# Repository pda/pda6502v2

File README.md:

pda6502v2
=========

pda6502v2 is a single-board homebrew computer built around the 8-bit
[6502][6502] CPU, varitions of which powered the venerable [Commodore 64][c64],
[Apple II][appleii], [Nintendo Entertainment System][nes] and lots more.

This repository contains all aspects of its development:

| Directory             | Description                      | Language / Tool |
| --------------------- | -------------------------------- | --------------- |
| [`kicad/`](kicad)     | hardware schematic / PCB design  | KiCad           |
| [`bifröst/`](bifröst) | BIFRÖST FPGA system controller   | Verilog         |
| [`os/`](os)           | pda6502v2 firmware/OS/software   | 6502 assembly   |
| [`emu/`](emu)         | pda6502v2 emulator               | Rust            |
| [`eeprog/`](eeprog)   | SPI EEPROM in-circuit programmer | C, Arduino C++  |

Hardware specifications
-----------------------

- 6502 CPU ([WDC 65C02][W65C02])
- “BIFRÖST” FPGA system controller ([Lattice ICE40HX4K][ice40])
- 512 KiB static RAM
- 2 x [6522 VIA][W65C22]; 4 x 8-bit ports; 32 GPIO pins
- [SID][sid] sound generator ([ARMSID][armsid])
- SPI controller (BIFRÖST FPGA)
- UART ([NXP SC28L92 dual UART][nxpuart])

Compared to original pda6502
----------------------------

pda6502v2 is redesigned from scratch to address the pain points encountered
creating and programming the original [pda6502][pda6502]
several years earlier:

* Tedious software/bootloader development cycle, physically removing and slowly
  reprogramming an EEPROM on every software iteration.
* Limited, very slow SPI communications (bit-banged via 6522 GPIO) not viable
  for SPI displays etc.
* No UART for serial console or other communications with modern systems.
* Inflexible address bus mapping with hard-wired logic gates.

These issues and more have been improved:

|                       | pda6502             | pda6502v2                             |
| --------------------- | ------------------- | ------------------------------------- |
| Bootloader / firmware | EEPROM              | In-circuit programmable Flash EEPROM  |
| SPI                   | 6522 bit-bang       | FPGA hardware accelerated             |
| UART                  | *none*              | Dual UART (SC28L92)                   |
| GPIO                  | 6522 VIA            | Dual 6522 VIA                         |
| Sound                 | *none*              | ARMSID (SID emulation)                |
| RAM                   | 32 KiB              | 512 KiB (FPGA can bank-switch)        |
| Clock                 | 1 MHz oscillator    | FPGA generated; variable              |
| Address decode logic  | 7400-series chips   | FPGA programmable                     |
| Voltage               | 5.0V                | 3.3V                                  |
| Schematic/layout tool | EAGLE               | KiCad                                 |

FPGA system controller: BIFRÖST
-------------------------------

An FPGA (Lattice ICE40HX4K-TQ144) acts as a system controller (dubbed BIFRÖST)
with three primary functions;

### System startup

Startup code is stored in an on-board SPI serial EEPROM (Microchip AT25M01)
which can be written from an external computer via SPI ICSP header.

(Microchip AT25M01 replaced by ON Semiconductor CAT25M01 due to availability).

BIFRÖST bootstraps the system by copying a fixed size/location bootloader from
serial EEPROM into main RAM before starting CPU.  The bootloader may load
further code/data from the serial EEPROM.

This solves the main pain point of version one, in which program/bootloader
development involved removing and rewriting an EEPROM on every development
iteration.

### Address logic

Mapping of the address space to SRAM and I/O chips is also handled by BIFRÖST.
This provide very low propagation time allowing for fast clock speed, and is
in-circuit programmable for flexible address space / logic design without
hardware changes.

BIFRÖST has the entire address bus, data bus, control signals and clock,
allowing for arbitrary address mapping. For example a control register could be
exposed for state-based mapping, e.g. memory layer switching like the Commodore
64.

### BIFRÖST chip selection / considerations

BIFRÖST is implemented as a Lattice ICE40HX4K-TQ144 FPGA with a Microchip
AT25M01 SPI flash EEPROM for configuration storage. The EEPROM also acts as
the 6502 system ROM, loaded into RAM by BIFRÖST during boot.

Any signal that can be routed through / controlled by BIFRÖST should be, so
that design decisions are pushed from hardware schematic and into FPGA HDL
which can be easily altered after assembly.

BIFRÖST needs the following signals:

| Signals                                                                       | Count   |
| ----------------------------------------------------------------------------- | ------- |
| Bus: `ADDR 0..15` + extended `ADDR 16..18`                                    | **19**  |
| SPI: `MISO`, `MOSI`, `SCLK`, `SS` x 8                                         | **11**  |
| 6502: `CLK` `RWB` `BE` `IRQB` `MLB` `NMIB` `RDY` `SOB` `SYNC` `VPB` `RESB`    | **10**  |
| UART: `CS`, `IM`, `IRQ`, `RDN`, `RXAIRQ`, `RXBIRQ`, `TXAIRQ`, `TXBIRQ`, `WRN` | **9**   |
| Bus: `DATA 0..7`                                                              | **8**   |
| VIA1 & VIA2: `CS`, `IRQ`                                                      | **4**   |
| SRAM `CS`                                                                     | **1**   |
| `CLOCKSRC` (in from oscillator)                                               | **1**   |
| `~RESET`                                                                      | **1**   |

This brings the total I/O pin requirement to at least 64.

The ICE40HX1K-VQ100 FPGA lacks PLL; PLL could be useful?

The TQ144 package includes PLL and has the same 0.5 mm pitch, so shouldn't be
materially harder to hand-solder.

The ICE40HX**4**K is bigger/better, with immaterial cost difference at this
volume.

RAM
---

Alliance Memory AS6C4008-55PCN 512K x 8 SRAM with 55ns access time at 2.7~5.5V
in a PDIP-32 package provides 512 KiB RAM.

This is 8 times larger than the 6502's 16-bit address space; access to RAM
beyond the first 64 KiB is managed by BIFRÖST.

(Earlier during system design, a pair of AS6C62256 32K x 8 PDIP-28 was chosen
to provide a less overkill and more era-appropriate 64 KiB of RAM, then lure of
1 MiB RAM made that 2 x 512 KiB, then the second 512 KiB was removed to make
PCB space for SID.

I/O
---

- SPI: 8 devices
- GPIO: 2 x 6522 VIA providing total of 4 x 8-bit ports
- Dual UART
- SID (ARMSID) sound

### SPI

BIFRÖST maps registers into the 6502 address space, implementing SPI master
similar to http://6502.org/users/andre/spi65b/index.html

This hardware SPI communication is orders of magnitude faster than 6522
bit-banging, making SPI display output more viable.

### GPIO

A pair of WDC W65C22S (6522) VIA provide two 8-bit GPIO ports each, as well as timers etc.

### UART

NXP SC28L92 3.3V dual UART (SC28L92A1A: PLC44-44 package)

Useful information on [UARTs: REPLACING THE 65C51 on 6502.org forums](http://forum.6502.org/viewtopic.php?f=4&t=4587).

### SID Sound

[ARMSID][armsid] emulates MOS6581 or MOS8580 SID.

I believe this will only function correctly when running at ~1 MHz.

An email reply from the creator re. voltage and clock:

> The ARMSID has its own LDO regulator, so it needs at least 3.45 V (max. 5.5 V) on pin 24 for proper operation.
> The value of the output signals is logic 3.3 V, the inputs are tolerant to 5 V. Therefore, it is not a problem to connect it to a 3.3 V system.
> The clock signal is designed for use in the C64, so it is guaranteed in the range of 0.985 to 1.023 MHz and directly controls the emulation rate (just like the original SID).
> Lower frequencies are not a problem, higher frequencies can disable emulation. All write and read operations should take at least 350ns for proper operation.

Power supply & reset
--------------------

TLV1117-33 LDO linear regulator brings 4.75V–15V down to the main 3.3V / 800mA
supply, used for all internal/external I/O.

LT3030 dual LDO linear regulator brings the 3.3V supply down to 2.5V / 750mA
and 1.2V / 250mA for the additional FPGA voltage requirements.

The In-Circuit System Programming (ICSP) header can power the AT25M01 SPI flash
EEPROM (1.7–5.5V) only, isolated from the rest of the system via 1N4148 Diode.

Maxim DS1818-5 “3.3V EconoReset with Pushbutton” handles holding RESET
active-low during power-on, brown-out, and when a RESET button is pressed.

Memory map
----------

Memory mapping is controlled by BIFRÖST, so it may be reconfigured.
Currently, everything is RAM except 0xD000–DFFF.

- `0xD400` SID (nobomi ARMSID)
- `0xDC00` VIA1 (WDC 65C22)
- `0xDC10` VIA2 (WDC 65C22)
- `0xDC20` UART (NXP SC28L92)

This roughly matches Commodore 64's I/O space.

Errata
------

R26 (0 ohm) and R27 (open) labels are swapped.
The one closer to LT3030 vreg is R26 and should be 0 ohm (jumper/shorted).
The one further from the LT3030 vreg is R27 and should be open (not connected).

EEPROM triple drama:
- 128 KiB isn't nearly enough; iCEstick has 4 MiB.
- missing pull-up on SPI CS to put FPGA into SPI master mode.
- MISO/MOSI lines from FPGA to EEPROM are swapped :(
The best solution to this mess is to leave the EEPROM footprint unpopulated,
and attach a small board to ICSP header with:
- a larger EEPROM,
- a 10K pull-up resistor on CS,
- a MISO/MOSI-correct ICSP header.
A prototype of this works using a Winbond W25Q80BVAIG 8Mbit SPI EEPROM.
(Silver lining: attempts to program the EEPROM while it's connected to the FPGA
have failed, despite efforts to make the FPGA tristate those SPI lines when not
in use. Being able to disconnect the EEPROM from the FPGA is useful. However
one of the pda6502v2 goals was uploading new 6502 code without touching the
board. Hopefully this can be fixed in Verilog.

RESET lines for BIFRÖST FPGA and the 6502 system are coupled.  This is a
terrible idea; BIFRÖST needs to reset the CPU without resetting itself.
Workaround: use a knife to physically cut the RESET trace coming from top-right
pin of RESET switch, next to pin 1 of ARMSID, and then airwire from EXT[0] to
6502 RESET.

[6502]: http://en.wikipedia.org/wiki/MOS_Technology_6502
[W65C02]: http://en.wikipedia.org/wiki/WDC_65C02
[W65C22]: http://en.wikipedia.org/wiki/WDC_65C22
[appleii]: https://en.wikipedia.org/wiki/Apple_II
[armsid]: https://www.nobomi.cz/8bit/armsid/index_en.php
[c64]: https://en.wikipedia.org/wiki/Commodore_64
[ice40]: https://www.latticesemi.com/iCE40
[nes]: https://en.wikipedia.org/wiki/Nintendo_Entertainment_System
[nxpuart]: https://www.nxp.com/products/interfaces/uarts/3-3-v-5-0-v-dual-universal-asynchronous-receiver-transmitter-duart:SC28L92
[sid]: https://en.wikipedia.org/wiki/MOS_Technology_6581
[pda6502]: https://github.com/pda/pda6502

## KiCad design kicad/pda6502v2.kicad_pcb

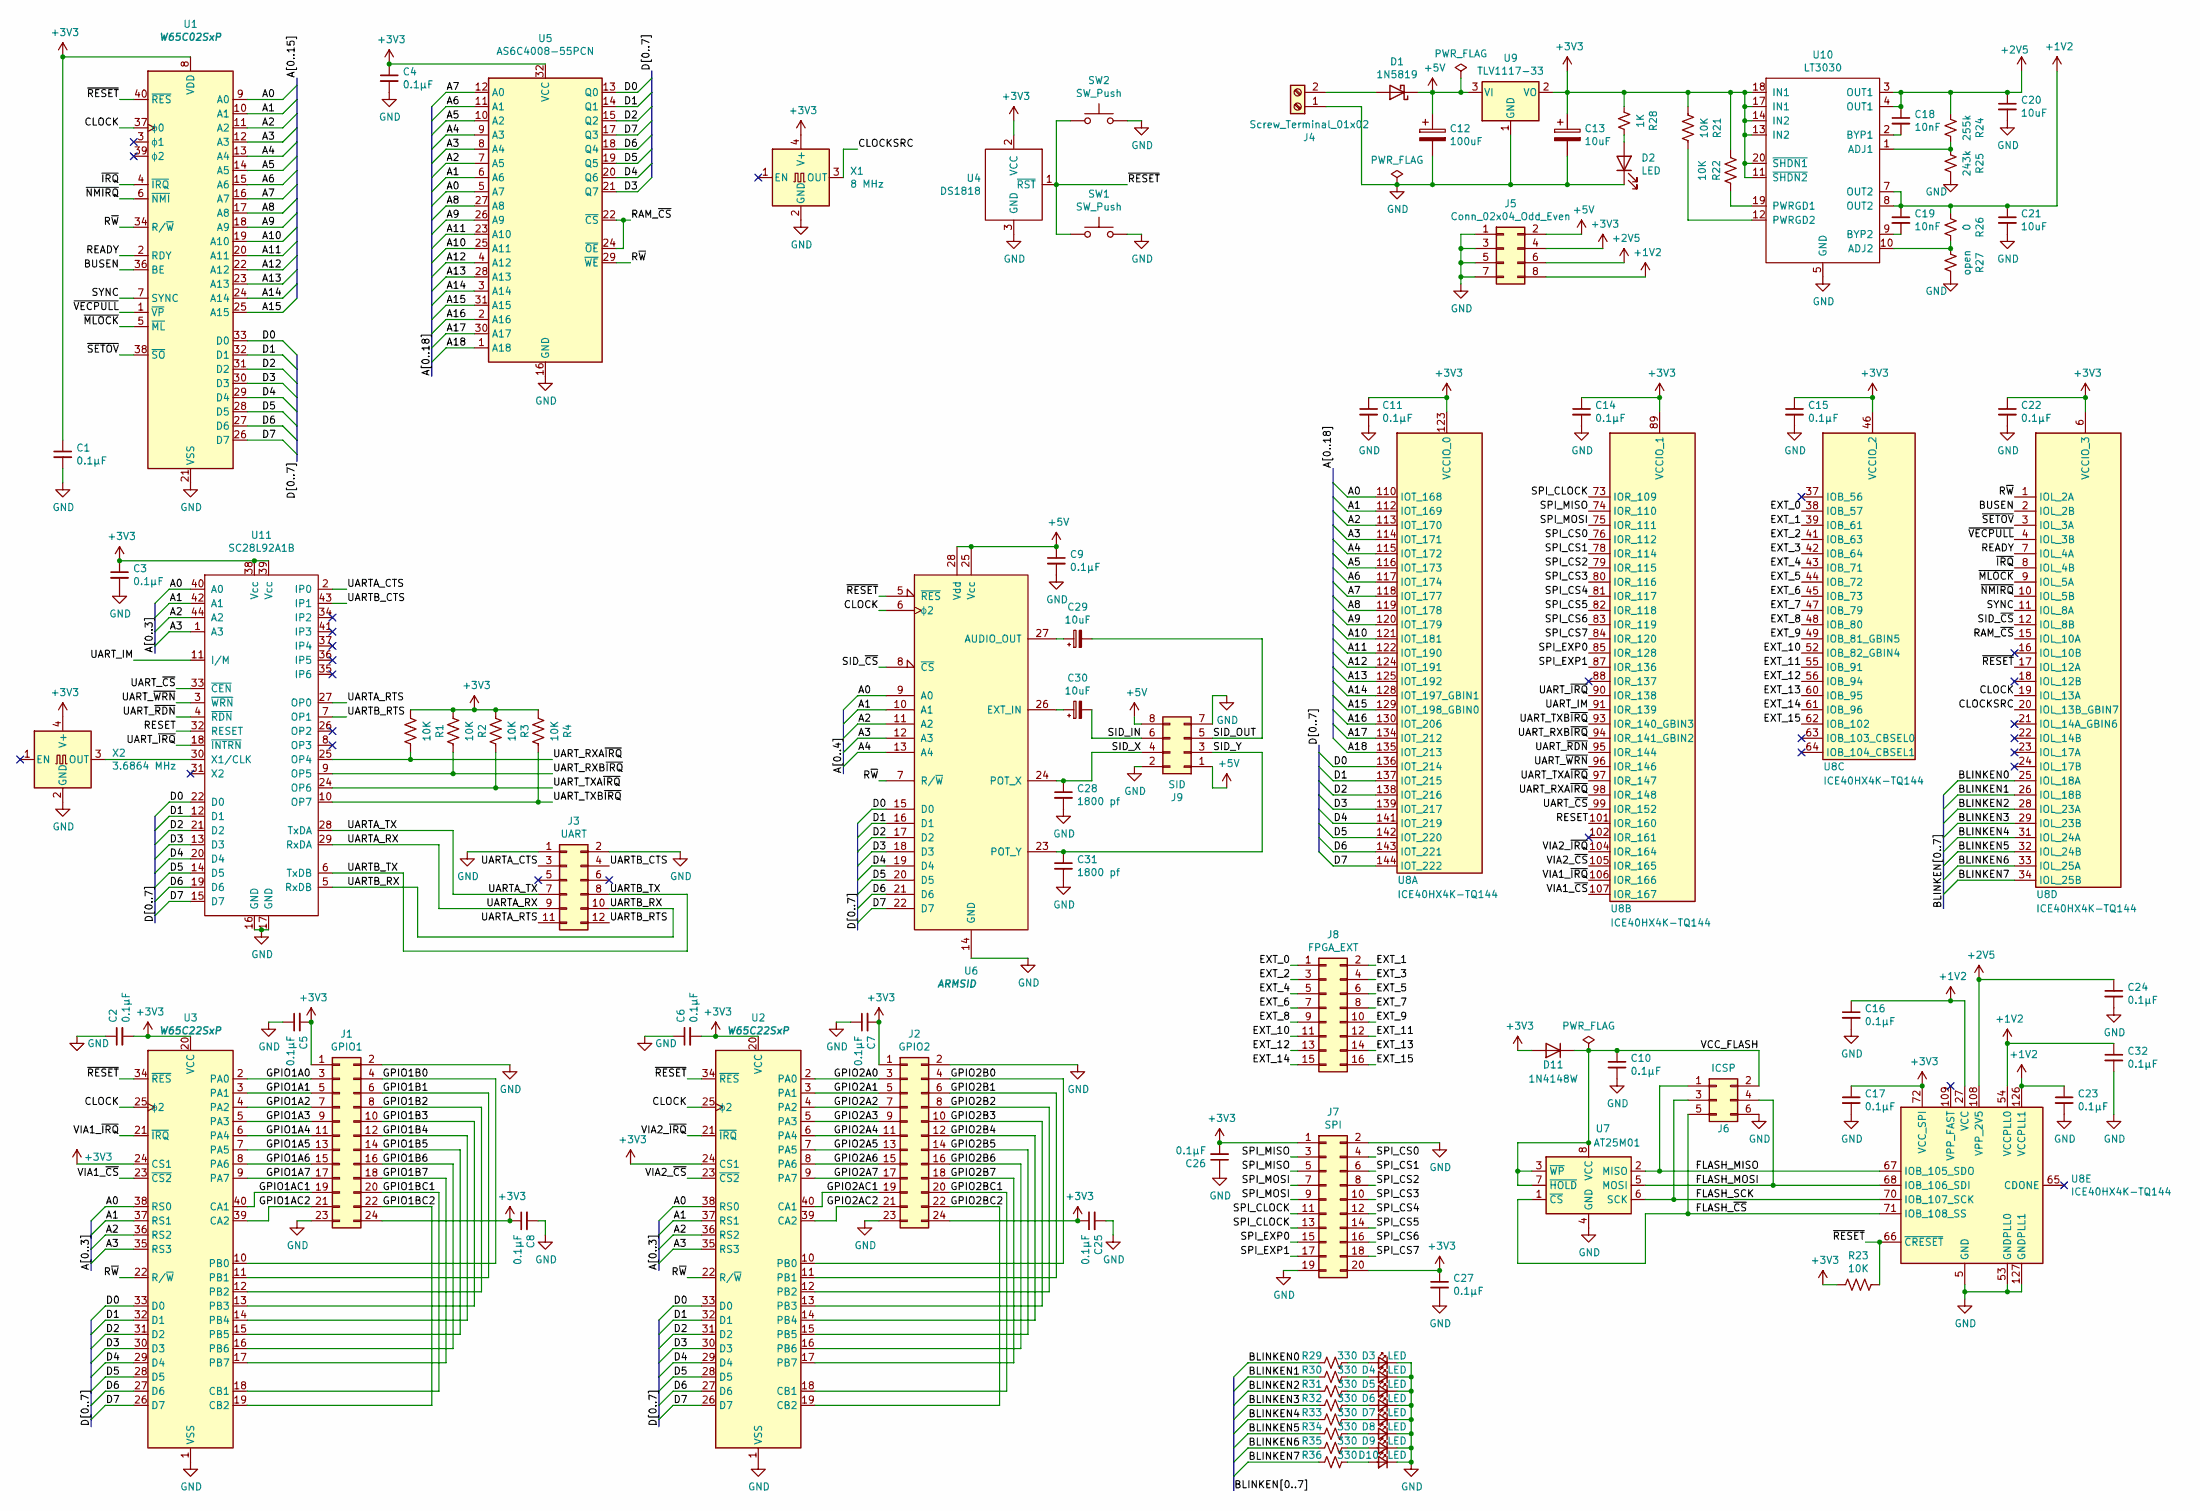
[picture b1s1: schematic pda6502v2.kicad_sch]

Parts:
C1, C2, C3, C4, C5, C6, C7, C8, C9, C10, C11, C14, C15, C16, C17, C22, C23, C24, C25, C26, C27, C32: 0.1μF; C_0805_2012Metric_Pad1.18x1.45mm_HandSolder
C12: 100uF; CP_Radial_D5.0mm_P2.00mm
C13: 10uF; CP_Radial_D5.0mm_P2.00mm
C18, C19: 10nF; C_0805_2012Metric_Pad1.18x1.45mm_HandSolder
C20, C21: 10uF; C_0805_2012Metric_Pad1.18x1.45mm_HandSolder
C28, C31: 1800 pf; C_0805_2012Metric_Pad1.18x1.45mm_HandSolder
C29, C30: 10uF; CP_EIA-3528-15_AVX-H_Pad1.50x2.35mm_HandSolder
D1: 1N5819; D_DO-41_SOD81_P10.16mm_Horizontal
D2: LED; LED_D3.0mm
D3, D4, D5, D6, D7, D8, D9, D10: LED; LED_0805_2012Metric_Pad1.15x1.40mm_HandSolder
D11: 1N4148W; D_SOD-123
J1: GPIO1; PinHeader_2x12_P2.54mm_Vertical
J2: GPIO2; PinHeader_2x12_P2.54mm_Vertical
J3: UART; PinHeader_2x06_P2.54mm_Vertical
J4: Screw_Terminal_01x02; TerminalBlock_Phoenix_MPT-0,5-2-2.54_1x02_P2.54mm_Horizontal
J5: Conn_02x04_Odd_Even; PinHeader_2x04_P2.54mm_Vertical
J6: ICSP; PinHeader_2x03_P2.54mm_Vertical
J7: SPI; PinHeader_2x10_P2.54mm_Vertical
J8: FPGA_EXT; PinHeader_2x08_P2.54mm_Vertical
J9: SID; PinHeader_2x04_P2.54mm_Vertical
R1, R2, R3, R4, R21, R22, R23: 10K; R_0805_2012Metric_Pad1.20x1.40mm_HandSolder
R24: 255k; R_0805_2012Metric_Pad1.20x1.40mm_HandSolder
R25: 243k; R_0805_2012Metric_Pad1.20x1.40mm_HandSolder
R26: 0; R_0805_2012Metric_Pad1.20x1.40mm_HandSolder
R27: open; R_0805_2012Metric_Pad1.20x1.40mm_HandSolder
R28: 1K; R_0805_2012Metric_Pad1.20x1.40mm_HandSolder
R29, R30, R31, R32, R33, R34, R35, R36: 330; R_0805_2012Metric_Pad1.20x1.40mm_HandSolder
SW1: SW_Push; SW_PUSH_6mm_H5mm
SW2: SW_Push; PinHeader_1x02_P2.54mm_Vertical
U1: W65C02SxP; DIP-40_W15.24mm
U2, U3: W65C22SxP; DIP-40_W15.24mm
U4: DS1818; SOT-23_Handsoldering
U5: AS6C4008-55PCN; DIP-32_W15.24mm
U6: ARMSID; DIP-28_W15.24mm_Socket
U7: AT25M01; SOIC-8_3.9x4.9mm_P1.27mm
U8: ICE40HX4K-TQ144; TQFP-144_20x20mm_P0.5mm
U9: TLV1117-33; SOT-223
U10: LT3030; HTSSOP-20-1EP_4.4x6.5mm_P0.65mm_EP2.85x4mm
U11: SC28L92A1B; PQFP-44_10x10mm_P0.8mm
X1: 8 MHz; Oscillator_SMD_EuroQuartz_XO53-4Pin_5.0x3.2mm
X2: 3.6864 MHz; Oscillator_SMD_EuroQuartz_XO53-4Pin_5.0x3.2mm

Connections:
+1V2: C16.1, C19.1, C21.1, C23.1, C32.1, J5.8, R26.2, U8.27 (VCC), U8.40 (VCC), U8.54 (VCCPLL0), U8.92 (VCC), U8.111 (VCC), U8.126 (VCCPLL1), U10.7 (OUT2), U10.8 (OUT2)
+2V5: C18.1, C20.1, C24.1, J5.6, R24.2, U8.108 (VPP_2V5), U10.3 (OUT1), U10.4 (OUT1)
+5V: C9.1, C12.1, D1.1 (K), J5.2, J9.1, J9.8, U6.25 (Vcc), U6.28 (Vdd), U9.3 (VI)
/A0: U1.9 (A0), U2.38 (RS0), U3.38 (RS0), U5.5 (A7), U6.9 (A0), U8.110 (IOT_168), U11.40 (A0)
/A1: U1.10 (A1), U2.37 (RS1), U3.37 (RS1), U5.6 (A6), U6.10 (A1), U8.112 (IOT_169), U11.42 (A1)
/A2: U1.11 (A2), U2.36 (RS2), U3.36 (RS2), U5.7 (A5), U6.11 (A2), U8.113 (IOT_170), U11.44 (A2)
/A3: U1.12 (A3), U2.35 (RS3), U3.35 (RS3), U5.8 (A4), U6.12 (A3), U8.114 (IOT_171), U11.1 (A3)
/A4: U1.13 (A4), U5.9 (A3), U6.13 (A4), U8.115 (IOT_172)
/A5: U1.14 (A5), U5.10 (A2), U8.116 (IOT_173)
/A6: U1.15 (A6), U5.11 (A1), U8.117 (IOT_174)
/A7: U1.16 (A7), U5.12 (A0), U8.118 (IOT_177)
/A8: U1.17 (A8), U5.27 (A8), U8.119 (IOT_178)
/A9: U1.18 (A9), U5.26 (A9), U8.120 (IOT_179)
/A10: U1.19 (A10), U5.25 (A11), U8.121 (IOT_181)
/A11: U1.20 (A11), U5.23 (A10), U8.122 (IOT_190)
/A12: U1.22 (A12), U5.4 (A12), U8.124 (IOT_191)
/A13: U1.23 (A13), U5.28 (A13), U8.125 (IOT_192)
/A14: U1.24 (A14), U5.3 (A14), U8.128 (IOT_197_GBIN1)
/A15: U1.25 (A15), U5.31 (A15), U8.129 (IOT_198_GBIN0)
/A16: U5.2 (A16), U8.130 (IOT_206)
/A17: U5.30 (A17), U8.134 (IOT_212)
/A18: U5.1 (A18), U8.135 (IOT_213)
/BLINKEN0: R29.2, U8.25 (IOL_18A)
/BLINKEN1: R30.2, U8.26 (IOL_18B)
/BLINKEN2: R31.2, U8.28 (IOL_23A)
/BLINKEN3: R32.2, U8.29 (IOL_23B)
/BLINKEN4: R33.2, U8.31 (IOL_24A)
/BLINKEN5: R34.2, U8.32 (IOL_24B)
/BLINKEN6: R35.2, U8.33 (IOL_25A)
/BLINKEN7: R36.2, U8.34 (IOL_25B)
/BUSEN: U1.36 (BE), U8.2 (IOL_2B)
/CLOCK: U1.37 (ϕ0), U2.25 (ϕ2), U3.25 (ϕ2), U6.6 (ϕ2), U8.19 (IOL_13A)
/CLOCKSRC: U8.20 (IOL_13B_GBIN7), X1.3 (OUT)
/D0: U1.33 (D0), U2.33 (D0), U3.33 (D0), U5.13 (Q0), U6.15 (D0), U8.136 (IOT_214), U11.22 (D0)
/D1: U1.32 (D1), U2.32 (D1), U3.32 (D1), U5.14 (Q1), U6.16 (D1), U8.137 (IOT_215), U11.12 (D1)
/D2: U1.31 (D2), U2.31 (D2), U3.31 (D2), U5.15 (Q2), U6.17 (D2), U8.138 (IOT_216), U11.21 (D2)
/D3: U1.30 (D3), U2.30 (D3), U3.30 (D3), U5.21 (Q7), U6.18 (D3), U8.139 (IOT_217), U11.13 (D3)
/D4: U1.29 (D4), U2.29 (D4), U3.29 (D4), U5.20 (Q6), U6.19 (D4), U8.141 (IOT_219), U11.20 (D4)
/D5: U1.28 (D5), U2.28 (D5), U3.28 (D5), U5.19 (Q5), U6.20 (D5), U8.142 (IOT_220), U11.14 (D5)
/D6: U1.27 (D6), U2.27 (D6), U3.27 (D6), U5.18 (Q4), U6.21 (D6), U8.143 (IOT_221), U11.19 (D6)
/D7: U1.26 (D7), U2.26 (D7), U3.26 (D7), U5.17 (Q3), U6.22 (D7), U8.144 (IOT_222), U11.15 (D7)
/EXT_0: J8.1, U8.38 (IOB_57)
/EXT_1: J8.2, U8.39 (IOB_61)
/EXT_2: J8.3, U8.41 (IOB_63)
/EXT_3: J8.4, U8.42 (IOB_64)
/EXT_4: J8.5, U8.43 (IOB_71)
/EXT_5: J8.6, U8.44 (IOB_72)
/EXT_6: J8.7, U8.45 (IOB_73)
/EXT_7: J8.8, U8.47 (IOB_79)
/EXT_8: J8.9, U8.48 (IOB_80)
/EXT_9: J8.10, U8.49 (IOB_81_GBIN5)
/EXT_10: J8.11, U8.52 (IOB_82_GBIN4)
/EXT_11: J8.12, U8.55 (IOB_91)
/EXT_12: J8.13, U8.56 (IOB_94)
/EXT_13: J8.14, U8.60 (IOB_95)
/EXT_14: J8.15, U8.61 (IOB_96)
/EXT_15: J8.16, U8.62 (IOB_102)
/FLASH_MISO: J6.1, U7.2 (MISO), U8.67 (IOB_105_SDO)
/FLASH_MOSI: J6.4, U7.5 (MOSI), U8.68 (IOB_106_SDI)
/FLASH_SCK: J6.3, U7.6 (SCK), U8.70 (IOB_107_SCK)
/FLASH_~CS: J6.5, U7.1 (~CS), U8.71 (IOB_108_SS)
/GPIO1A0: J1.3, U3.2 (PA0)
/GPIO1A1: J1.5, U3.3 (PA1)
/GPIO1A2: J1.7, U3.4 (PA2)
/GPIO1A3: J1.9, U3.5 (PA3)
/GPIO1A4: J1.11, U3.6 (PA4)
/GPIO1A5: J1.13, U3.7 (PA5)
/GPIO1A6: J1.15, U3.8 (PA6)
/GPIO1A7: J1.17, U3.9 (PA7)
/GPIO1AC1: J1.19, U3.40 (CA1)
/GPIO1AC2: J1.21, U3.39 (CA2)
/GPIO1B0: J1.4, U3.10 (PB0)
/GPIO1B1: J1.6, U3.11 (PB1)
/GPIO1B2: J1.8, U3.12 (PB2)
/GPIO1B3: J1.10, U3.13 (PB3)
/GPIO1B4: J1.12, U3.14 (PB4)
/GPIO1B5: J1.14, U3.15 (PB5)
/GPIO1B6: J1.16, U3.16 (PB6)
/GPIO1B7: J1.18, U3.17 (PB7)
/GPIO1BC1: J1.20, U3.18 (CB1)
/GPIO1BC2: J1.22, U3.19 (CB2)
/GPIO2A0: J2.3, U2.2 (PA0)
/GPIO2A1: J2.5, U2.3 (PA1)
/GPIO2A2: J2.7, U2.4 (PA2)
/GPIO2A3: J2.9, U2.5 (PA3)
/GPIO2A4: J2.11, U2.6 (PA4)
/GPIO2A5: J2.13, U2.7 (PA5)
/GPIO2A6: J2.15, U2.8 (PA6)
/GPIO2A7: J2.17, U2.9 (PA7)
/GPIO2AC1: J2.19, U2.40 (CA1)
/GPIO2AC2: J2.21, U2.39 (CA2)
/GPIO2B0: J2.4, U2.10 (PB0)
/GPIO2B1: J2.6, U2.11 (PB1)
/GPIO2B2: J2.8, U2.12 (PB2)
/GPIO2B3: J2.10, U2.13 (PB3)
/GPIO2B4: J2.12, U2.14 (PB4)
/GPIO2B5: J2.14, U2.15 (PB5)
/GPIO2B6: J2.16, U2.16 (PB6)
/GPIO2B7: J2.18, U2.17 (PB7)
/GPIO2BC1: J2.20, U2.18 (CB1)
/GPIO2BC2: J2.22, U2.19 (CB2)
/RAM_~CS: U5.22 (~CS), U5.24 (~OE), U8.15 (IOL_10A)
/READY: U1.2 (RDY), U8.7 (IOL_4A)
/RESET: U8.101 (IOR_160), U11.32 (RESET)
/R~W: U1.34 (R/~W), U2.22 (R/~W), U3.22 (R/~W), U5.29 (~WE), U6.7 (R/~W), U8.1 (IOL_2A)
/SID_IN: C30.2, J9.6
/SID_OUT: C29.2, J9.5
/SID_X: C28.1, J9.4, U6.24 (POT_X)
/SID_Y: C31.1, J9.3, U6.23 (POT_Y)
/SID_~CS: U6.8 (~CS), U8.12 (IOL_8B)
/SPI_CLOCK: J7.11, J7.13, U8.73 (IOR_109)
/SPI_CS0: J7.4, U8.76 (IOR_112)
/SPI_CS1: J7.6, U8.78 (IOR_114)
/SPI_CS2: J7.8, U8.79 (IOR_115)
/SPI_CS3: J7.10, U8.80 (IOR_116)
/SPI_CS4: J7.12, U8.81 (IOR_117)
/SPI_CS5: J7.14, U8.82 (IOR_118)
/SPI_CS6: J7.16, U8.83 (IOR_119)
/SPI_CS7: J7.18, U8.84 (IOR_120)
/SPI_EXP0: J7.15, U8.85 (IOR_128)
/SPI_EXP1: J7.17, U8.87 (IOR_136)
/SPI_MISO: J7.3, J7.5, U8.74 (IOR_110)
/SPI_MOSI: J7.7, J7.9, U8.75 (IOR_111)
/SYNC: U1.7 (SYNC), U8.11 (IOL_8A)
/UARTA_CTS: J3.3, U11.2 (IP0)
/UARTA_RTS: J3.11, U11.27 (OP0)
/UARTA_RX: J3.9, U11.29 (RxDA)
/UARTA_TX: J3.7, U11.28 (TxDA)
/UARTB_CTS: J3.4, U11.43 (IP1)
/UARTB_RTS: J3.12, U11.7 (OP1)
/UARTB_RX: J3.10, U11.5 (RxDB)
/UARTB_TX: J3.8, U11.6 (TxDB)
/UART_IM: U8.91 (IOR_139), U11.11 (I/M)
/UART_RXA~IRQ: R1.1, U8.98 (IOR_148), U11.25 (OP4)
/UART_RXB~IRQ: R2.1, U8.94 (IOR_141_GBIN2), U11.9 (OP5)
/UART_TXA~IRQ: R3.1, U8.97 (IOR_147), U11.24 (OP6)
/UART_TXB~IRQ: R4.1, U8.93 (IOR_140_GBIN3), U11.10 (OP7)
/UART_~CS: U8.99 (IOR_152), U11.33 (~CEN)
/UART_~IRQ: U8.90 (IOR_138), U11.18 (~INTRN)
/UART_~RDN: U8.95 (IOR_144), U11.4 (~RDN)
/UART_~WRN: U8.96 (IOR_146), U11.3 (~WRN)
/VCC_FLASH: C10.1, D11.1 (K), J6.2, U7.3 (~WP), U7.7 (~HOLD), U7.8 (VCC)
/VIA1_~CS: U3.23 (~CS2), U8.107 (IOR_167)
/VIA1_~IRQ: U3.21 (~IRQ), U8.106 (IOR_166)
/VIA2_~CS: U2.23 (~CS2), U8.105 (IOR_165)
/VIA2_~IRQ: U2.21 (~IRQ), U8.104 (IOR_164)
/~IRQ: U1.4 (~IRQ), U8.8 (IOL_4B)
/~MLOCK: U1.5 (~ML), U8.9 (IOL_5A)
/~NMIRQ: U1.6 (~NMI), U8.10 (IOL_5B)
/~RESET: R23.1, SW1.1, SW2.2, U1.40 (~RES), U2.34 (~RES), U3.34 (~RES), U4.1 (~RST), U6.5 (~RES), U8.17 (IOL_12A), U8.66 (~CRESET)
/~SETOV: U1.38 (~SO), U8.3 (IOL_3A)
/~VECPULL: U1.1 (~VP), U8.4 (IOL_3B)
unnamed: C18.2, U10.2 (BYP1)
unnamed: C19.2, U10.9 (BYP2)
unnamed: C29.1, U6.27 (AUDIO_OUT)
unnamed: C30.1, U6.26 (EXT_IN)
unnamed: D1.2 (A), J4.2
unnamed: D2.2 (A), R28.1
unnamed: D3.2 (A), R29.1
unnamed: D4.2 (A), R30.1
unnamed: D5.2 (A), R31.1
unnamed: D6.2 (A), R32.1
unnamed: D7.2 (A), R33.1
unnamed: D8.2 (A), R34.1
unnamed: D9.2 (A), R35.1
unnamed: D10.2 (A), R36.1
unnamed: R21.1, U10.12 (PWRGD2)
unnamed: R22.1, U10.19 (PWRGD1)
unnamed: R24.1, R25.2, U10.1 (ADJ1)
unnamed: R26.1, R27.2, U10.10 (ADJ2)
unnamed: U11.30 (X1/CLK), X2.3 (OUT)

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
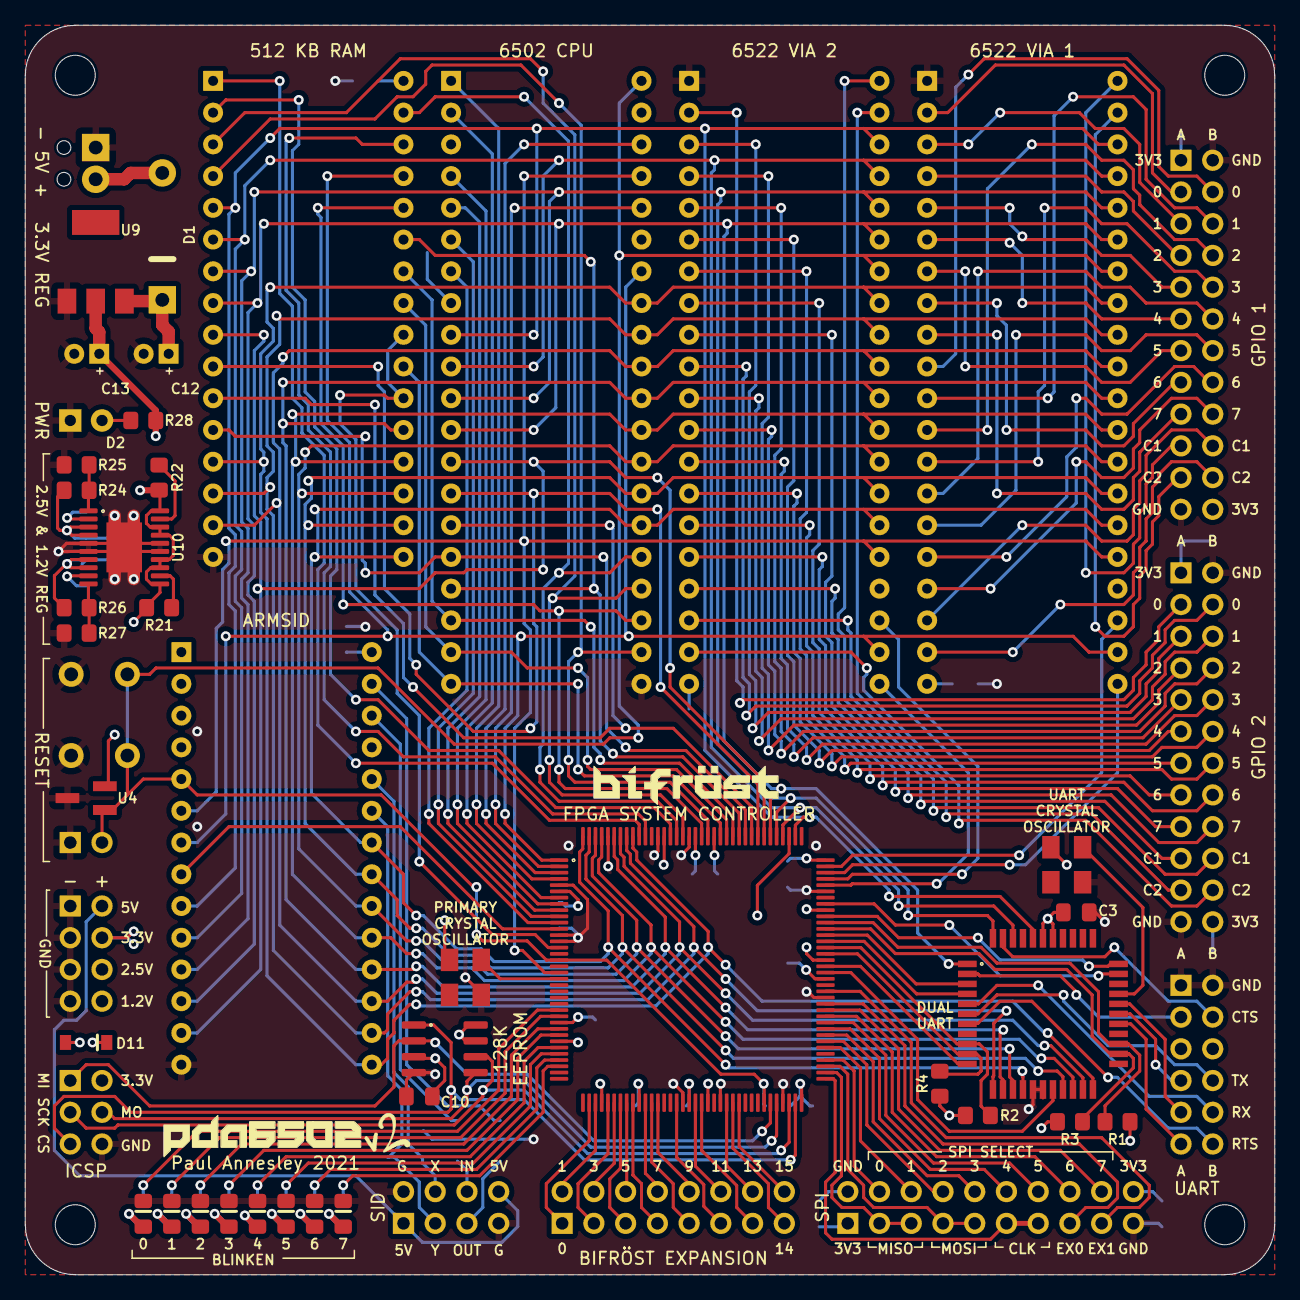
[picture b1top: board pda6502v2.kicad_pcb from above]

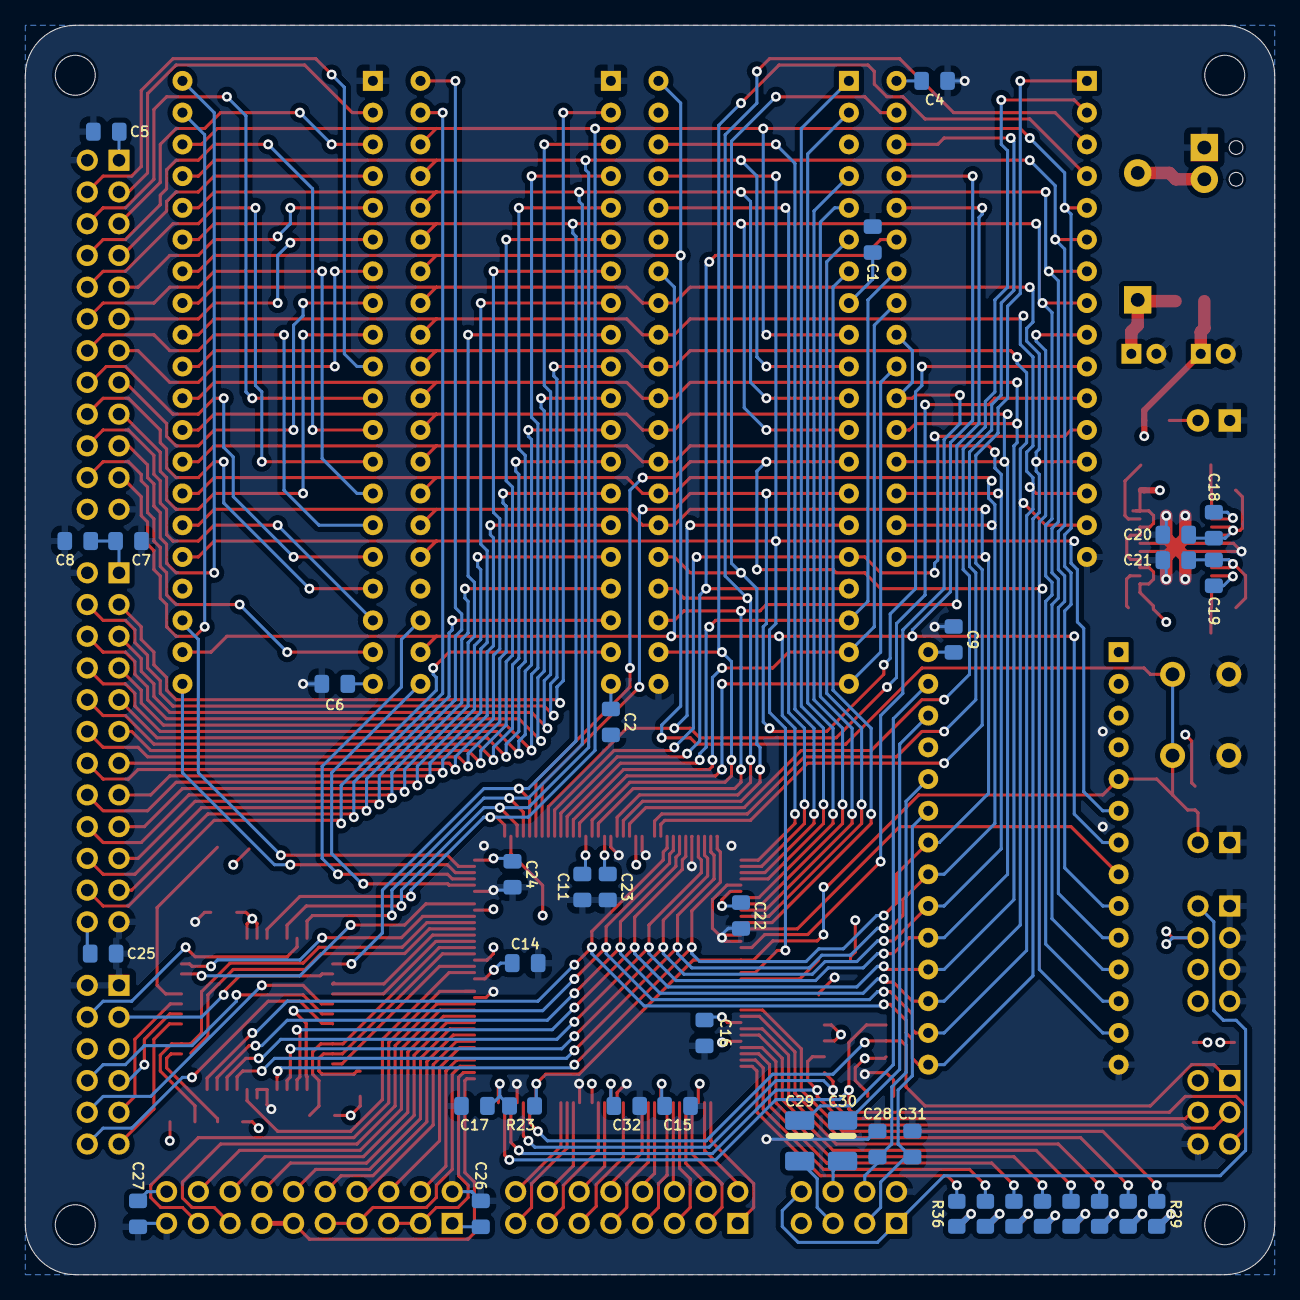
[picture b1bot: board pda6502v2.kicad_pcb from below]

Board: 4 copper layers, 100.0 x 100.0 mm, 87 parts (37 on the bottom side), 173 nets.

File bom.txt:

Id   Designator                            Package                                                  Quantity  Designation
[M] 4    C30,C29                               CP_EIA-3528-15_AVX-H_Pad1.50x2.35mm_HandSolder           2         10uF
[M] 5    U7                                    SOIC-8_3.9x4.9mm_P1.27mm                                 1         CAT25M01
[M] 6    C31,C28                               C_0805_2012Metric_Pad1.18x1.45mm_HandSolder              2         1800pF
[M] 7    C21,C20                               C_0805_2012Metric_Pad1.18x1.45mm_HandSolder              2         10uF
[M] 8    C19,C18                               C_0805_2012Metric_Pad1.18x1.45mm_HandSolder              2         10nF
[M] 9    C14,C32,C9,C27,C26,C25,C7,C6,C24,...  C_0805_2012Metric_Pad1.18x1.45mm_HandSolder              22        0.1μF
[M] 10   J4                                    TerminalBlock_Phoenix_MPT-0,5-2-2.54_1x02_P2.54mm_Ho...  1         Screw_Terminal_01x02
[M] 11   D1                                    D_DO-41_SOD81_P10.16mm_Horizontal                        1         1N5819
[M] 12   U9                                    SOT-223                                                  1         TLV1117-33
[M] 13   C13                                   CP_Radial_D5.0mm_P2.00mm                                 1         10uF
[M] 14   C12                                   CP_Radial_D5.0mm_P2.00mm                                 1         100uF
[M] 15   D2                                    LED_D3.0mm                                               1         LED
[M] 16   U10                                   HTSSOP-20-1EP_4.4x6.5mm_P0.65mm_EP2.85x4mm               1         LT3030
[M] 17   U4                                    SOT-23_Handsoldering                                     1         DS1818
[M] 18   SW2                                   PinHeader_1x02_P2.54mm_Vertical                          1         SW_Push
[M] 19A  R24                                   R_0805_2012Metric_Pad1.20x1.40mm_HandSolder              1         255k 1%
[M] 19B  R25                                   R_0805_2012Metric_Pad1.20x1.40mm_HandSolder              1         243k 1%
[M] 19C  R26                                   R_0805_2012Metric_Pad1.20x1.40mm_HandSolder              1         0 (jumper)
[-] 19D  R27                                   R_0805_2012Metric_Pad1.20x1.40mm_HandSolder              1         (open)
[M] 20   R3,R22,R21,R4,R23,R2,R1               R_0805_2012Metric_Pad1.20x1.40mm_HandSolder              7         10K
[M] 21   R28                                   R_0805_2012Metric_Pad1.20x1.40mm_HandSolder              1         1K
[M] 21A  R36,R35,R34,R33,R32,R31,R30,R29       R_0805_2012Metric_Pad1.20x1.40mm_HandSolder              8         330 ohm
[M] 22   SW1                                   SW_PUSH_6mm_H5mm                                         1         SW_Push
[M] 23   U8                                    TQFP-144_20x20mm_P0.5mm                                  1         ICE40HX4K-TQ144
[M] 24   U11                                   PQFP-44_10x10mm_P0.8mm                                   1         SC28L92A1B
[M] 25   U5                                    DIP-32_W15.24mm                                          1         AS6C4008-55PCN
[M] 26   X1                                    Oscillator_SMD_5.0x3.2mm_HandSolder                      1         8 MHz
[M] 27   X2                                    Oscillator_SMD_5.0x3.2mm_HandSolder                      1         3.6864 MHz
[M] 28   U3,U2                                 DIP-40_W15.24mm                                          2         W65C22SxP
[M] 29   U1                                    DIP-40_W15.24mm                                          1         W65C02SxP
[M] 30   J1                                    PinHeader_2x12_P2.54mm_Vertical                          1         GPIO1
[M] 31   J2                                    PinHeader_2x12_P2.54mm_Vertical                          1         GPIO2
[M] 32   J3                                    PinHeader_2x06_P2.54mm_Vertical                          1         UART
[M] 33   J7                                    PinHeader_2x10_P2.54mm_Vertical                          1         SPI
[M] 34   J8                                    PinHeader_2x08_P2.54mm_Vertical                          1         FPGA_EXT
[M] 35   J9                                    PinHeader_2x04_P2.54mm_Vertical                          1         SID
[M] 36   D3,D10,D9,D8,D7,D6,D5,D4              LED_0805_2012Metric_Pad1.15x1.40mm_HandSolder            8         LED
[M] 37   D11                                   D_SOD-123                                                1         1N4148W
[M] 38   J6                                    PinHeader_2x03_P2.54mm_Vertical                          1         ICSP
[M] 39   J5                                    PinHeader_2x04_P2.54mm_Vertical                          1         Conn_02x04_Odd_Even
[R] 40   U6                                    DIP-28_W15.24mm_Socket                                   1         ARMSID


M: Mouser
R: Retrocomp

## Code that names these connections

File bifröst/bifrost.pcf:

set_io rw       1
set_io busen    2
set_io setov    3
set_io vecpull  4
set_io ready    7
set_io irq      8
set_io mlock    9
set_io nmirq   10
set_io sync    11

# set_io reset_fpga 17

set_io clock    20
set_io clockout 19

set_io leds[0] 34
set_io leds[1] 33
set_io leds[2] 32
set_io leds[3] 31
set_io leds[4] 29
set_io leds[5] 28
set_io leds[6] 26
set_io leds[7] 25

set_io flash_mosi 67
set_io flash_miso 68
set_io flash_sck  70
set_io flash_cs   71

set_io spi_clock 73
set_io spi_miso  74
set_io spi_mosi  75
set_io spi_cs[0] 76
set_io spi_cs[1] 78
set_io spi_cs[2] 79
set_io spi_cs[3] 80
set_io spi_cs[4] 81
set_io spi_cs[5] 82
set_io spi_cs[6] 83
set_io spi_cs[7] 84
set_io spi_exp0  85
set_io spi_exp1  87

set_io -pullup yes uart_irq     90
set_io uart_im      91
set_io uart_txbirq  93
set_io uart_rxbirq  94
set_io uart_rdn     95
set_io uart_wrn     96
set_io uart_txairq  97
set_io uart_rxairq  98
set_io uart_cs      99
set_io reset_inv   101

set_io via2_irq 104
set_io via2_cs  105
set_io via1_irq 106

set_io via1_cs  107

set_io sid_cs   12
set_io ram_cs   15

set_io addr[0]  110
set_io addr[1]  112
set_io addr[2]  113
set_io addr[3]  114
set_io addr[4]  115
set_io addr[5]  116
set_io addr[6]  117
set_io addr[7]  118
set_io addr[8]  119
set_io addr[9]  120
set_io addr[10] 121
set_io addr[11] 122
set_io addr[12] 124
set_io addr[13] 125
set_io addr[14] 128
set_io addr[15] 129
set_io addr[16] 130
set_io addr[17] 134
set_io addr[18] 135

set_io data[0] 136
set_io data[1] 137
set_io data[2] 138
set_io data[3] 139
set_io data[4] 141
set_io data[5] 142
set_io data[6] 143
set_io data[7] 144

set_io ext[0]  38
set_io ext[1]  39
set_io ext[2]  41
set_io ext[3]  42
set_io ext[4]  43
set_io ext[5]  44
set_io ext[6]  45
set_io ext[7]  47
set_io ext[8]  48
set_io ext[9]  49
set_io ext[10] 52
set_io ext[11] 55
set_io ext[12] 56
set_io ext[13] 60
set_io ext[14] 61
set_io ext[15] 62

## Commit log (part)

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2017-03-19 hardware: new blank KiCad project.
2017-03-19 pda6502v2 KiCad library with SAMD21J18A-AU
2017-03-31 hardware: WIP: glue schematic (CPLD address decode).
2017-04-04 pda6502v2 block diagram; WIP.
2017-04-04 spi65-b/.gitignore for Xilinx ISE
2017-04-04 spi65-b: ISE project, pinout constraints updated for XC2C64A-VQ44.
2017-04-09 README.md: CPLD speculation updated; XC2C128A etc.
2017-04-10 hardware: CPLD_XC2C128A_VQ100 in part library.
2017-04-14 hardware: CPU sub-schematic.
2021-03-11 README updates; no microcontroller; CPLD bootloader.
2021-04-10 Delete WIP KiCad schematic from April 2017
    It had some nice starts, with heirarchical sheets for 6522 GPIO etc, but
    was based on CPLD rather than FPGA, and had issues with latest KiCad
    versions/libraries which aren't really worth resolving.
2021-04-11 kicad/.gitignore from github/gitignore/KiCad.gitignore
2021-05-01 README: 64 KiB RAM; 2 x Alliance AS6C62256-55PCN
2021-05-29 README updates; keeping up with changed during schematic capture etc.
2021-06-03 WIP: remove PMOD. SMD LDO. Layout updates.
2021-06-03 Headers for SPI and EXT (FPGA expansion)
2021-06-04 Rearranged FPGA pin allocations for easier routing
2021-06-05 Routing begins; FPGA to EXT & SPI headers.
2021-06-05 Routing WIP; UART
2021-06-07 Routing; power, ground vias, UART/osc, reset button/header, etc.
2021-06-16 BLINKEN routed
2021-06-17 more routing; SID connector, misc power etc.
2021-06-23 ARMSID routing improvements; fewer vias, straighter tracks.
2021-06-23 More routing, more stuck.
2021-07-31 Track routing tweaks / optimisation.
2021-07-31 Cleanup (auto): Delete dangling tracks
2021-08-12 PA initials and "v2" on PCB, plus some tweaks.
2021-08-13 bifröst dir, with verilog code for blinken splash.
2021-08-17 CAT25M01 datasheet; AT25M01 succumbed to COVID chip shortage
    CAT25M01 is the ON Semiconductor clone of Microchip AT25M01, I believe.
2021-08-29 bom.txt
2021-08-29 bifröst: early WIP on boot EEPROM→RAM.
2021-09-07 eeprog: WIP spike, with Makefile & macOS/brew env file
2021-09-07 bifröst: test/demo blinken on iCEstick (working)
2021-09-09 eeprog: extracted sneaky 2am hexdump to hexdump.{c,h}
2021-09-09 eeprog write <filename> command; works.
2021-09-10 eeprog: stdout for general output, stderr for errors.
2021-09-14 README: Errata describes EEPROM SNAFU.
2021-09-17 eeprog: fast spi_write (no read) for faster upload.
2021-09-25 eeprog: off-by-one in hexdump ASCII output
2021-09-25 eeprog: sector-test.c; testing sector/page/byte loops
2021-09-25 eeprog: Arduino version of EEPROM programmer
2021-09-25 docs: iCE40 Programming and Configuration Technical Note
2021-09-25 bifröst: BLINKEN LEDs register flipped so MSB is left-most.
2021-09-25 bifröst: bifrost.v with testbench, not doing anything much yet.
    Attempting to put SPI outputs into tri-state so that eeprog can drive
    them, but yosys doesn't (fully?) support tri-state..?
    Meanwhile, eeprog has learned to hold RESET active during SPI
    operations.
2021-09-27 bifröst: output 1 MHz clockout by dividing 8 MHz input.
2021-09-29 bifröst: boot.v fixes; offset width, leave outputs in Hi-Z.
2021-09-29 bifröst: boot.v state machine simplified, states named w/ localparam.
2021-10-02 bifröst: lots of fixes; seems to testbench & synth okay
2021-10-04 eeprog: cmd_write prints ? to serial if Serial.read() fails
2021-10-04 eeprog: cmd_download
2021-10-04 bifröst: divide 6502 clock down to 31,250 Hz for now.
2021-10-07 bifröst: busen comment corrected
2021-10-07 bifröst: Makefile for %.asc uses %.pcf instead of bifrost.pcf
2021-10-08 bifröst adec: only ram_cs guarded by clock=HIGH
    GARTHWILSON reckon's RAM should be guarded by PHI2.
    Seems like clocked devices (6522 etc) don't need this.
    Hopefully that applies to SID/ARMSID too (it's clocked).
    http://forum.6502.org/viewtopic.php?t=511
2021-10-08 docs: block diagram updated, less wrong.
2021-10-09 eeprog: disable RESET during writes (messes with SPI?)
    With RESET _not_ being held during reset, ICSP writes by eeprog are
    succeeding while FPGA is connected. I guess this means the FPGA SPI
    lines are correctly tri-stating to Hi-Z now.
2021-10-09 bifröst: blinken can be written to by 6502 at $DE00
2021-10-09 spi65-b deleted, ima write my own in Verilog
2021-10-09 eeprog: remove/reduce unnecessary delay()s
2021-10-09 eeprog: fix CRLF for cmd_write want/got message
2021-10-09 bifröst: boot uses 1 MHz clockout, not 4 MHz (was failing)
2021-10-12 bifröst: fix adec; enable RAM during HIGH clock, not LOW!
    I was attempting to heed this advice, but flipped the logic:
    > Notice in the diagram above that Φ2 is involved with the RAM select
    > but nothing else. You must have a way to make sure RAM cannot be
    > written when Φ2 is low!
    — http://wilsonminesco.com/6502primer/addr_decoding.html
2021-10-12 os: tidy up simple BLINKEN code
2021-10-13 bifröst: irq signal drive (only by via2_irq for now)
2021-10-13 os: bounce blinken back and forth using VIA2 timer interrupts.
2021-10-16 os: blinken uses ASL/LSR to avoid CLC before ROL/ROR
2021-10-17 os: unused code deleted from uart.s
2021-10-24 bifröst: BLINKEN can show reg, DATA, ADDR_LO, ADDR_HI, IRQ.
2021-10-25 bifröst & os: blinken timer shifted to VIA1
    VIA1_IRQ to FPGA solder joint is fixed, so it can now be used. This
    change successfully tests it working as a timer. It also refactors the
    via.s constants to separate the 16-bit base address of each chip from
    the 4-bit register addresses therein.
2021-10-26 os: HandleInterrupt predicates JSR BlinkenTick on VIA1 IFR T1
2021-10-26 os: memory.conf has bss segment
2021-10-29 os: UartRxInterrupt stops pulling from FIFO when full
2021-10-29 os: indentation update; 16 col label, 24 col instruction
2021-10-30 os: UartRxBufRead blocks/polls if carry bit set.
2021-10-30 os: HandleInterrupt refactored
2021-11-05 os: UartEcho uses UartTxBufWrite; UartPutc deleted.
2021-11-06 bifröst: 6502 reset moved from ext[0] to ext[15]
    The fixup wire is soldered on the underside of the board now, rather
    than alligator-clipped across the top. It seemed to make more sense to
    use the last EXT pin, rather than the first, partly because its on the
    inner side of the connector.
2021-11-07 os/shell: skip ShellCmd handling for empty cmdbuf
2021-11-09 os: WIP game of life; rendering a grid to ASCII/UART.
2021-11-11 os: UART at 115,200 baud, was 9600
2021-11-13 os: game of life refactored to use actual maths and comments.
    Previous code was a 2am special.
2021-11-14 os: TermCursorHide, TermCursorShow
    DECTCEM: Text Cursor Enable Mode Show
    h = high = show
    l = low = hide
2021-11-14 os: zeropage.s with R0..F registers and ZP_BLNKAUX
2021-11-14 os: use R0, R1 etc names for $00, $01 etc zeropage addresses.
    As defined in zeropage.s
2021-11-14 os: LifeTick eachneighbour loop shortens code
2021-11-14 os: LifeMain has shorter delay between ticks/generations
2021-11-15 os: StrEq moved to new string.s
2021-11-23 bifröst: hardware SPI!
2021-11-23 bifröst: run 6502 system at 1 MHz
2021-11-23 os: game of life delay removed; slow enough at 1MHz
2021-11-27 os: SID tunes early progress.
2021-12-01 os: UartEcho deleted, unused
2021-12-13 os: uart.s code comment fixes/improvements.
2022-01-03 emu: early WIP on an emulator written in Rust
2022-01-09 emu: Instruction opcode table
2022-06-24 emu: Cpu Debug tweaked to match Rust default/derived
2022-06-25 emu: asm tweaks
2022-06-26 emu: Assembler labels, org, listing, LDX, refactoring, etc.
2022-06-27 emu: main tidied & commented
2022-06-27 emu: bus tidied, read16 extracted to cpu
2022-06-28 README: update intro, repo ToC, comparison etc.
2022-06-29 emu: Debug for Opcode upper-cases Mnemonic (Nop→NOP)
2022-07-01 emu: Assembler listing displays upper-case Mnemonics
2022-07-01 emu: cpu tests use new op() helper for brevity
2022-07-01 emu: Assembler.print_listing to easily tap into method chains
2022-07-01 emu: INX ZP mode implemented, tested. Cpu tests use Assembler now.
2022-07-02 emu: isa::operand_length, Cpu.consume_operand, UnwrapOpValue
2022-07-09 emu: asm listing prefixes immediate values with hash
2022-07-09 emu: JMP handles more address modes, tweaks to INX and unit tests
2022-07-19 emu: W65C02S manual §3.1 Reset says SR=xx1101xx
2022-07-19 emu: Cpu.read_operand_value() extracted from repeated pattern
2022-07-19 emu: CPU test moved from src/cpu.rs to tests/cpu.rs
    These are integration tests; they're using the CPU with a real Bus,
    Assembler etc.
2022-08-25 emu: BCC implemented (TODO: asm handle abs→rel)
2022-10-03 emu: asm branches implement relative addressing (including labels)
2022-10-06 emu: asm has data(Vec<u8>) method to add arbitrary data
2022-10-09 emu: BMI implemented
2022-10-09 emu: BPL implemented
2022-10-16 emu: CLC, CLD, CLI, CLV, SEC, SED, SEI implemented
2022-10-27 kicad: add kicad_pro, kicad_sch & rescue files
    I can only guess what these are, they're sitting around as untracked
    changes, may as well commit them.
2022-11-27 emu: Cpu push_addr() and push() refactored out of BRK
2023-04-07 emu: DEC implemented
2023-04-07 emu: INY implemented
2023-04-09 emu: INC implemented
2023-04-09 emu: JSR and RTS implemented
2023-04-14 emu: LSR implemented
2023-04-14 emu: asm consistently uses `-> &mut Self`
2023-04-14 emu: PHP and PLP implemented
2023-04-22 emu: RTI implemented (and BRK return addr fixed)
2023-04-28 emu: STA & STX & STY implemented
2023-04-30 emu: BRK & RTI corrected
    As discovered via:
    https://github.com/TomHarte/ProcessorTests/tree/main/6502
2023-05-01 emu: rename `sp` to `s` (stack pointer)
    This matches the naming used by the rest of the world.
2023-06-28 emu: refactor so Cpu doesn't ref/own Bus
2023-06-28 emu: new mon::Monitor prints cpu state and next opcode
    This should eventually become an interactive monitor/debugger
2023-06-29 emu: mon::Monitor shows next opcode+operand
2023-10-14 kicad: 6502-kicad-library updated
    I should perhaps make this a git submodule, or just vendor it, or just
    copy in the parts I need.
2023-10-14 kicad: schematic format version 20211123->20230121 (KiCad 7.0)
2023-10-15 kicad: schematic Electrical Rules Checker fixes
    Use updated 6502-kicad-library symbols, including their 6522 instead of
    our own. The symbol size/pins etc moved around, schematic adjusted.
    Use new built-in capacitor symbols instead of rescued olf CP-Device.
2023-10-16 kicad: PCB DRC fixes; only require 1 spoke of thermal relief
    Various pads only have space for a single spoke to the copper GND fill,
    and that's fine.
    There's still various warnings.
2024-03-12 Buildkite CI
2024-05-07 emu: 65C02 opcodes: PHX PHY PLX PLY
    http://www.6502.org/tutorials/65c02opcodes.html
2024-05-10 emu: colour monitor output, and beginnings of UART
2024-06-02 emu: working! interrupts, UART as UDP port 6502, SID random for GoL.
2024-06-06 buildkite: install test collector, begin integrating secret
2024-06-06 buildkite: mount-buildkite-agent into container for secrets
2024-06-06 buildkite: fix YAML multiline newlines
2024-06-06 buildkite: more secrets debugging
